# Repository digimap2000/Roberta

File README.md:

# Roberta
Comau NS16 Industrial Robot Conversion

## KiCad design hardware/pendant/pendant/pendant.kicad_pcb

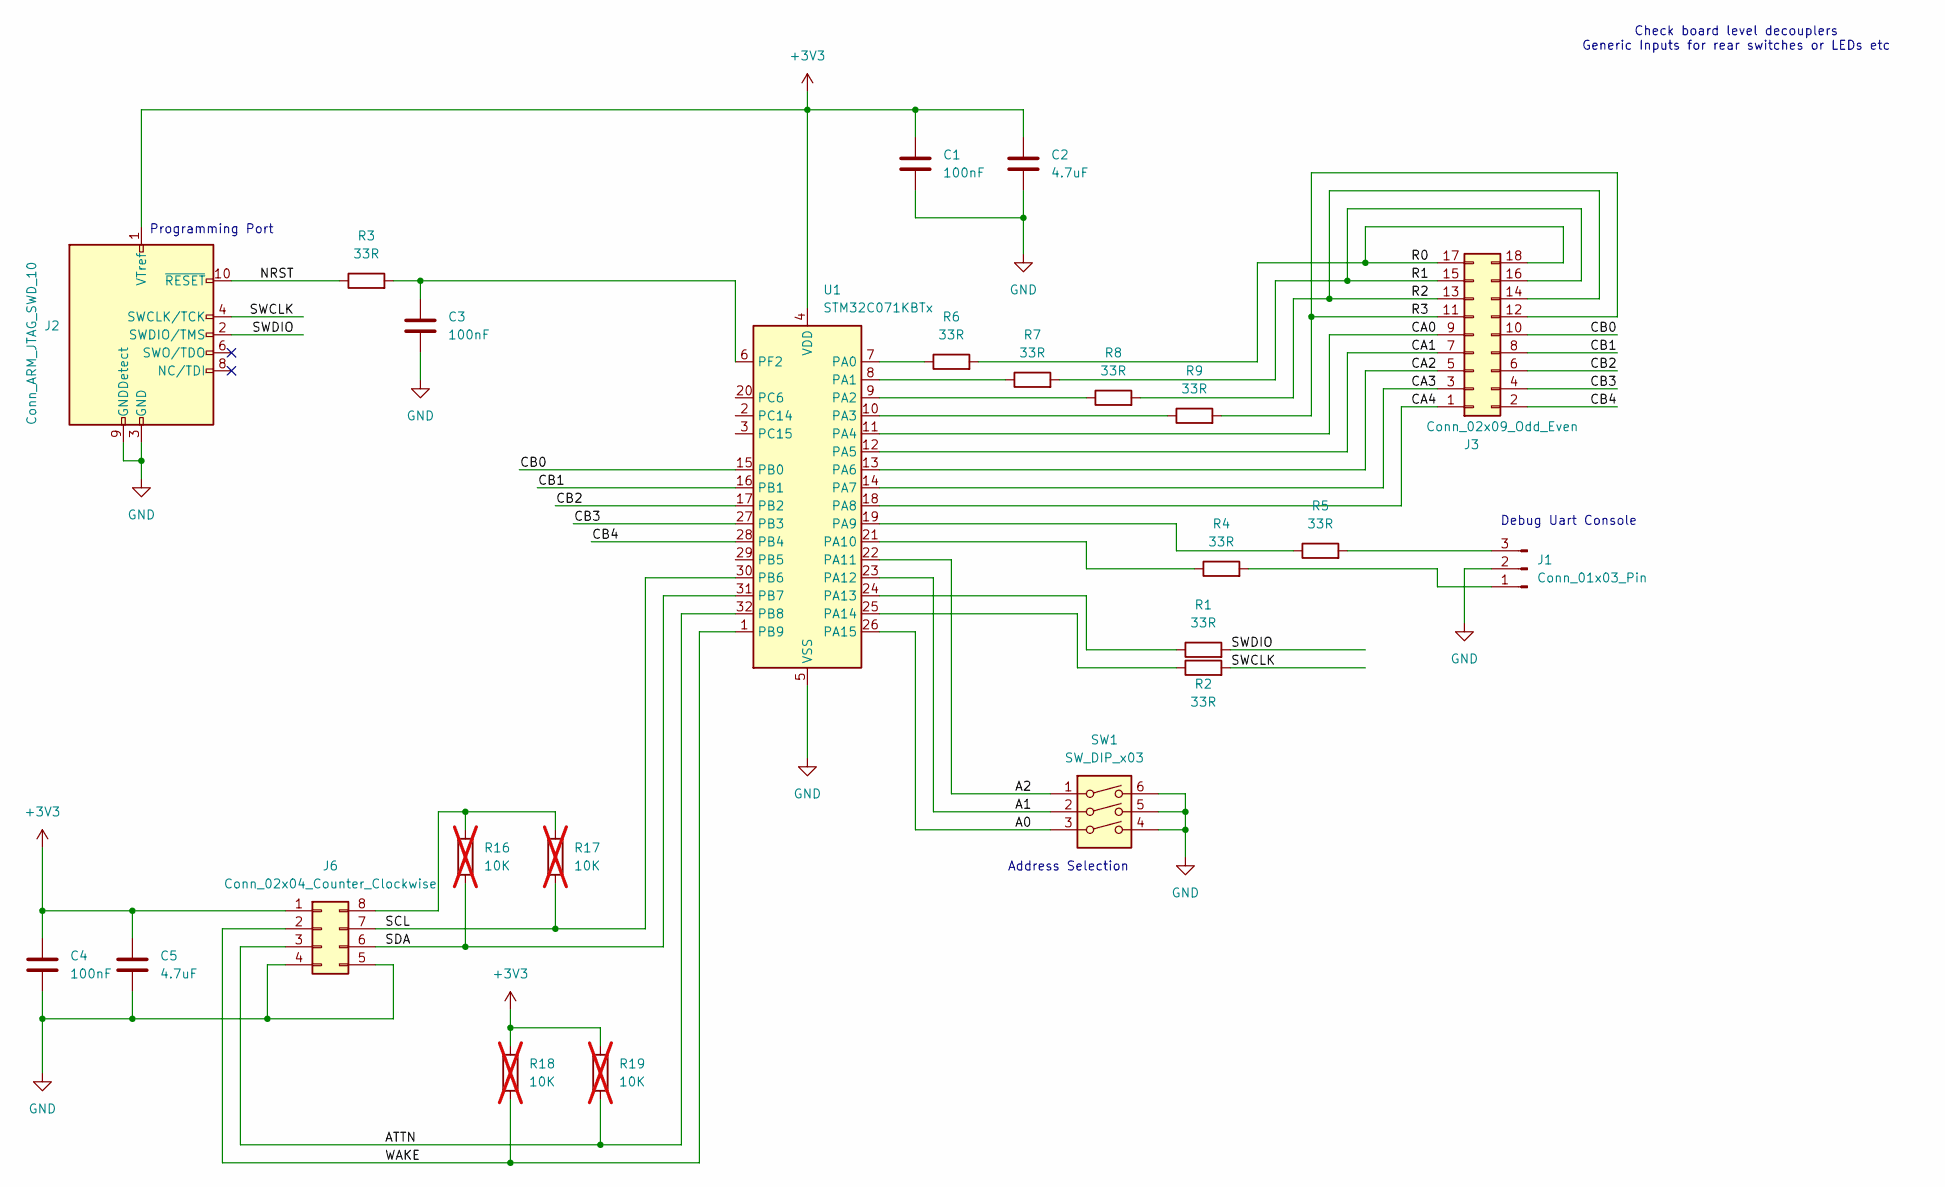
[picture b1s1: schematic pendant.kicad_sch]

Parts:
C1, C3, C4: 100nF; C_0805_2012Metric
C2, C5: 4.7uF; C_0805_2012Metric
J1: Conn_01x03_Pin; PinHeader_1x03_P2.54mm_Vertical
J2: Conn_ARM_JTAG_SWD_10; Tag-Connect_TC2050-IDC-FP_2x05_P1.27mm_Vertical
J3: Conn_02x09_Odd_Even; PinHeader_2x09_P2.54mm_Horizontal
J6: Conn_02x04_Counter_Clockwise; PinHeader_2x04_P2.54mm_Vertical
R1, R2, R3, R4, R5, R6, R7, R8, R9: 33R; R_0805_2012Metric
R16, R17, R18, R19: 10K; R_0805_2012Metric; not fitted
SW1: SW_DIP_x03; DIP-6_W7.62mm
U1: STM32C071KBTx; LQFP-32_7x7mm_P0.8mm

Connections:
+3V3: C1.1, C2.1, C4.1, C5.1, J2.1 (VTref), J6.1, R18.2, R19.2, U1.4 (VDD)
/A0: SW1.3, U1.26 (PA15)
/A1: SW1.2, U1.23 (PA12)
/A2: SW1.1, U1.22 (PA11)
/ATTN: J6.3, R19.1, U1.32 (PB8)
/CA0: J3.9, U1.11 (PA4)
/CA1: J3.7, U1.12 (PA5)
/CA2: J3.5, U1.13 (PA6)
/CA3: J3.3, U1.14 (PA7)
/CA4: J3.1, U1.18 (PA8)
/CB0: J3.10, U1.15 (PB0)
/CB1: J3.8, U1.16 (PB1)
/CB2: J3.6, U1.17 (PB2)
/CB3: J3.4, U1.27 (PB3)
/CB4: J3.2, U1.28 (PB4)
/NRST: J2.10 (~RESET), R3.1
/R0: J3.17, J3.18, R6.2
/R1: J3.15, J3.16, R7.2
/R2: J3.13, J3.14, R8.2
/R3: J3.11, J3.12, R9.2
/SCL: J6.7, R17.1, U1.30 (PB6)
/SDA: J6.6, R16.1, U1.31 (PB7)
/SWCLK: J2.4 (SWCLK/TCK), R2.2
/SWDIO: J2.2 (SWDIO/TMS), R1.2
/WAKE: J6.2, R18.1, U1.1 (PB9)
GND: C1.2, C2.2, C3.2, C4.2, C5.2, J1.2, J2.3 (GND), J2.5 (GND), J2.9 (GNDDetect), J6.4, J6.5, SW1.4, SW1.5, SW1.6, U1.5 (VSS)
unnamed: J1.1, R4.2
unnamed: J1.3, R5.2
unnamed: J6.8, R16.2, R17.2
unnamed: R6.1, U1.7 (PA0)
unnamed: R7.1, U1.8 (PA1)
unnamed: R8.1, U1.9 (PA2)
unnamed: R9.1, U1.10 (PA3)
unnamed: R5.1, U1.19 (PA9)
unnamed: R4.1, U1.21 (PA10)
unnamed: R1.1, U1.24 (PA13)
unnamed: R2.1, U1.25 (PA14)
unnamed: C3.1, R3.2, U1.6 (PF2)

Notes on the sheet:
Debug Uart Console
Check board level decouplers Generic Inputs for rear switches or LEDs etc
Programming Port
Address Selection

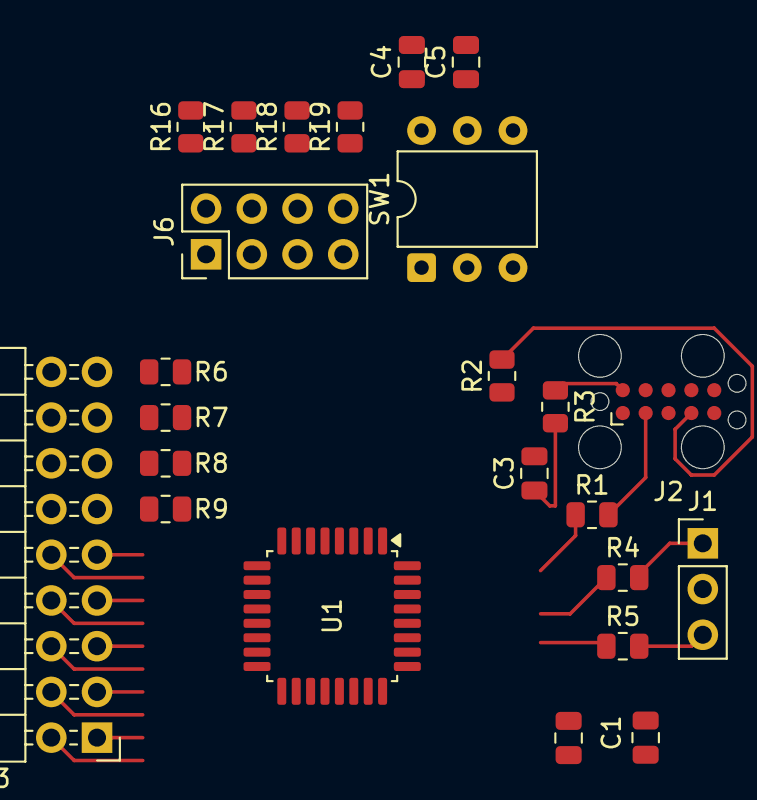
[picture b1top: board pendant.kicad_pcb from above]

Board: 2 copper layers, 24 parts (0 on the bottom side), 38 nets.

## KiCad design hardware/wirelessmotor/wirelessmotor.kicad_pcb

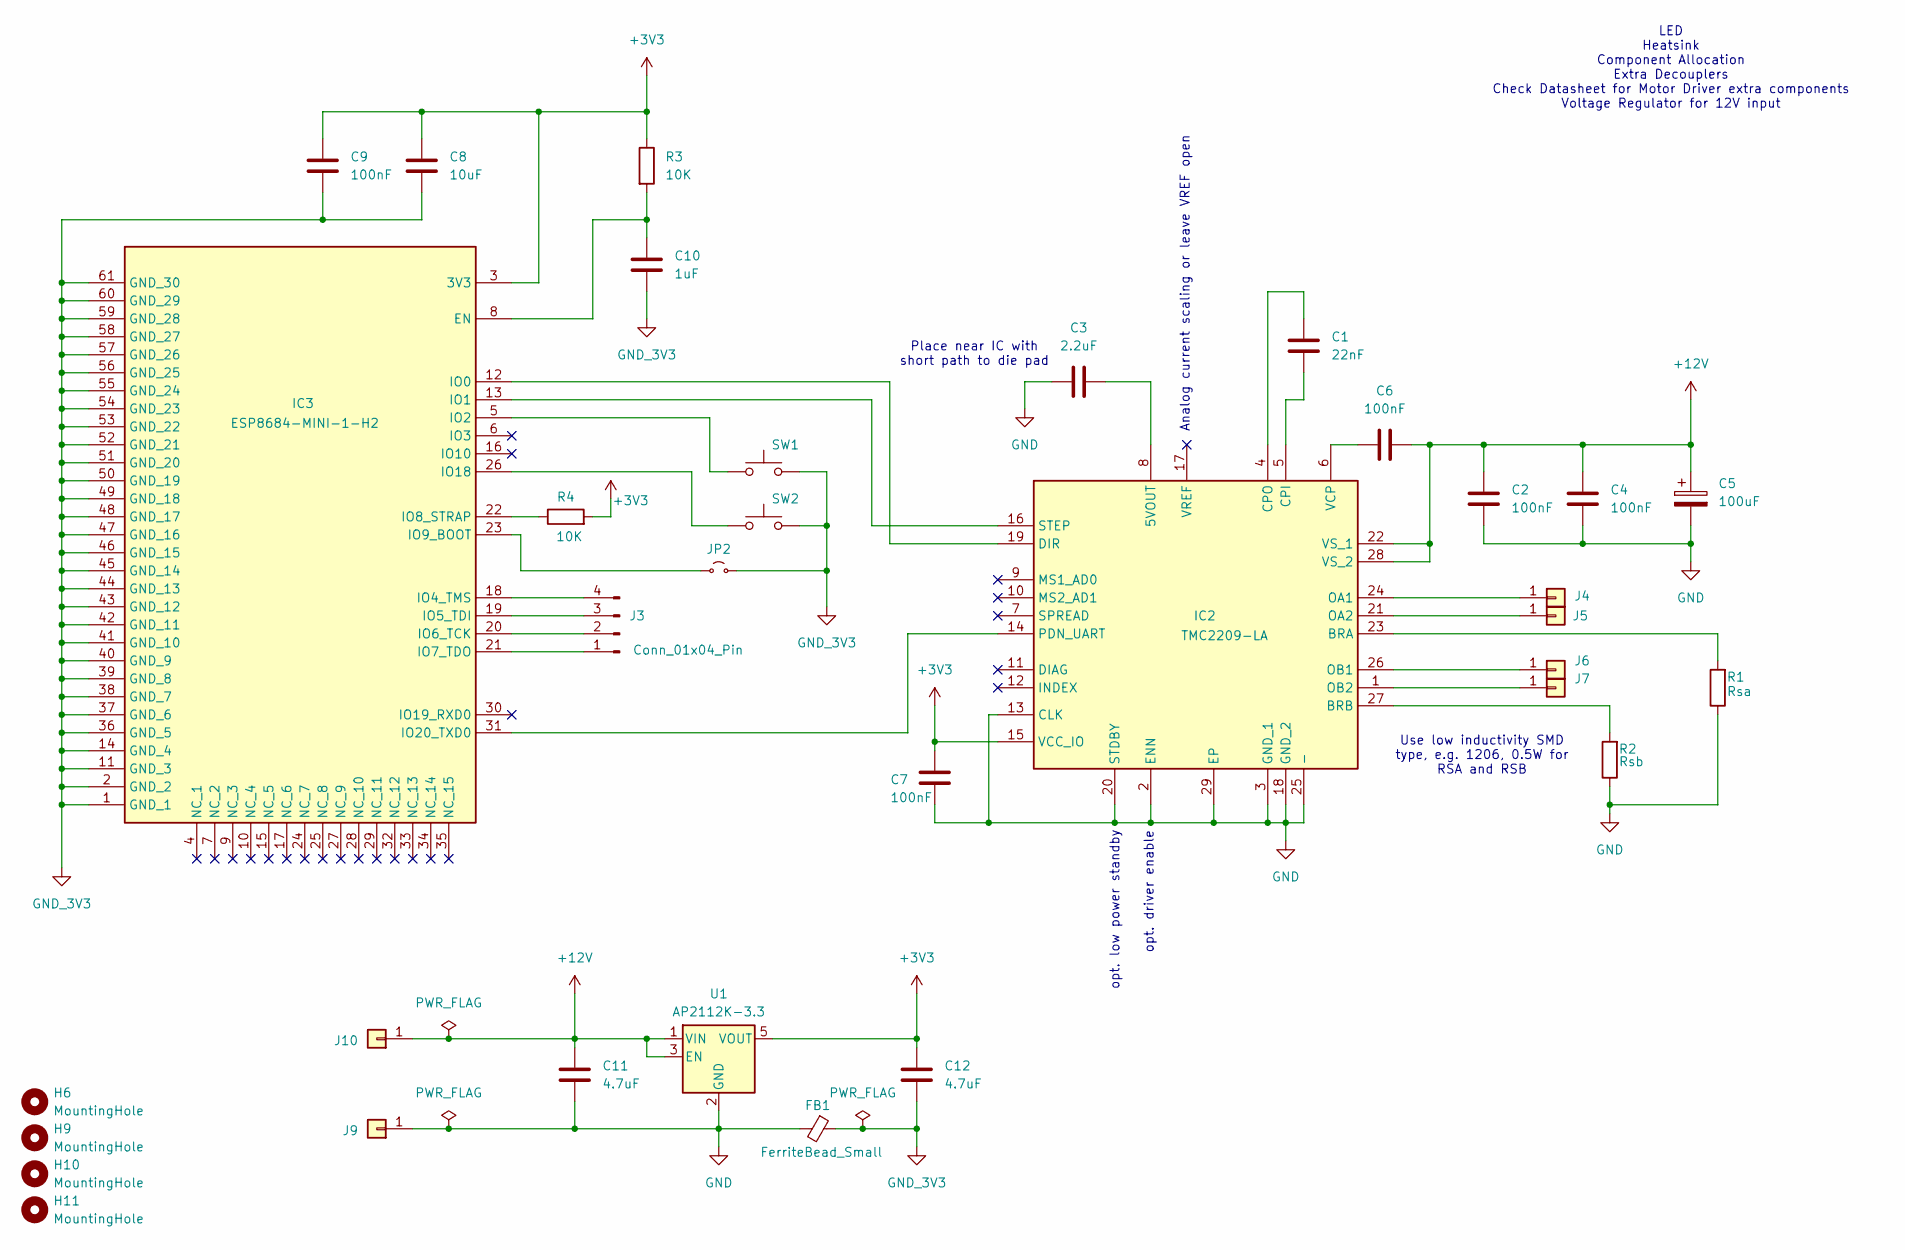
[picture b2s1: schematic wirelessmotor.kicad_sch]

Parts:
C1: 22nF; C_0603_1608Metric
C2, C4, C6, C7, C9: 100nF; C_0603_1608Metric
C3: 2.2uF; C_0603_1608Metric
C5: 100uF; C_0603_1608Metric
C8: 10uF; C_0603_1608Metric
C10: 1uF; C_0603_1608Metric
C11, C12: 4.7uF; C_0603_1608Metric
FB1: FerriteBead_Small; L_Walsin_WLFM201209x
H6, H9, H10, H11: MountingHole; MountingHole_2.2mm_M2_DIN965_Pad
IC2: TMC2209-LA; QFN50P500X500X90-29N; Manufacturer_Part_Number TMC2209-LA; Mouser Part Number 700-TMC2209-LA
IC3: ESP8684-MINI-1-H2; ESP8684MINI1H2; Manufacturer_Part_Number ESP8684-MINI-1-H2; Mouser Part Number 356-ESP8684MINI1H2
J3: Conn_01x04_Pin; PinHeader_1x04_P1.27mm_Vertical
J4: OA1; TestPoint_THTPad_2.5x2.5mm_Drill1.2mm
J5: OA2; TestPoint_THTPad_2.5x2.5mm_Drill1.2mm
J6: 0B1; TestPoint_THTPad_2.5x2.5mm_Drill1.2mm
J7: OB2; TestPoint_THTPad_2.5x2.5mm_Drill1.2mm
J9: 0V; TestPoint_THTPad_2.5x2.5mm_Drill1.2mm
J10: +12V; TestPoint_THTPad_2.5x2.5mm_Drill1.2mm
JP2: Jumper_2_Small_Open; PinHeader_1x02_P1.27mm_Vertical
R1: Rsa; R_0603_1608Metric
R2: Rsb; R_0603_1608Metric
R3, R4: 10K; R_0603_1608Metric
SW1, SW2: SW_Push; PTS636SK43JSMTRLFS
U1: AP2112K-3.3; SOT-23-5

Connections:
+3V3: C7.1, C8.1, C9.1, C12.2, IC2.15 (VCC_IO), IC3.3 (3V3), R3.1, R4.2, U1.5 (VOUT)
+12V: C2.1, C4.1, C5.1, C6.2, C11.2, IC2.22 (VS_1), IC2.28 (VS_2), J10.1, U1.1 (VIN), U1.3 (EN)
GND: C2.2, C3.1, C4.2, C5.2, C7.2, C11.1, FB1.2, IC2.2 (ENN), IC2.3 (GND_1), IC2.13 (CLK), IC2.18 (GND_2), IC2.20 (STDBY), IC2.25 (-), IC2.29 (EP), J9.1, R1.1, R2.1, U1.2 (GND)
GND_3V3: C8.2, C9.2, C10.2, C12.1, FB1.1, IC3.1 (GND_1), IC3.2 (GND_2), IC3.11 (GND_3), IC3.14 (GND_4), IC3.36 (GND_5), IC3.37 (GND_6), IC3.38 (GND_7), IC3.39 (GND_8), IC3.40 (GND_9), IC3.41 (GND_10), IC3.42 (GND_11), IC3.43 (GND_12), IC3.44 (GND_13), IC3.45 (GND_14), IC3.46 (GND_15), IC3.47 (GND_16), IC3.48 (GND_17), IC3.49 (GND_18), IC3.50 (GND_19), IC3.51 (GND_20), IC3.52 (GND_21), IC3.53 (GND_22), IC3.54 (GND_23), IC3.55 (GND_24), IC3.56 (GND_25), IC3.57 (GND_26), IC3.58 (GND_27), IC3.59 (GND_28), IC3.60 (GND_29), IC3.61 (GND_30), JP2.2 (B), SW1.2, SW2.2
unnamed: C3.2, IC2.8 (5VOUT)
unnamed: IC2.23 (BRA), R1.2
unnamed: IC2.27 (BRB), R2.2
unnamed: C1.2, IC2.5 (CPI)
unnamed: C1.1, IC2.4 (CPO)
unnamed: IC2.19 (DIR), IC3.12 (IO0)
unnamed: IC2.24 (OA1), J4.1
unnamed: IC2.21 (OA2), J5.1
unnamed: IC2.26 (OB1), J6.1
unnamed: IC2.1 (OB2), J7.1
unnamed: IC2.14 (PDN_UART), IC3.31 (IO20_TXD0)
unnamed: IC2.16 (STEP), IC3.13 (IO1)
unnamed: C6.1, IC2.6 (VCP)
unnamed: C10.1, IC3.8 (EN), R3.2
unnamed: IC3.5 (IO2), SW1.1
unnamed: IC3.18 (IO4_TMS), J3.4
unnamed: IC3.19 (IO5_TDI), J3.3
unnamed: IC3.20 (IO6_TCK), J3.2
unnamed: IC3.21 (IO7_TDO), J3.1
unnamed: IC3.22 (IO8_STRAP), R4.1
unnamed: IC3.23 (IO9_BOOT), JP2.1 (A)
unnamed: IC3.26 (IO18), SW2.1

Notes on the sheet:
LED Heatsink Component Allocation Extra Decouplers Check Datasheet for Motor Driver extra components Voltage Regulator for 12V input
Use low inductivity SMD type, e.g. 1206, 0.5W for RSA and RSB
opt. low power standby
Place near IC with short path to die pad
Analog current scaling or leave VREF open
opt. driver enable

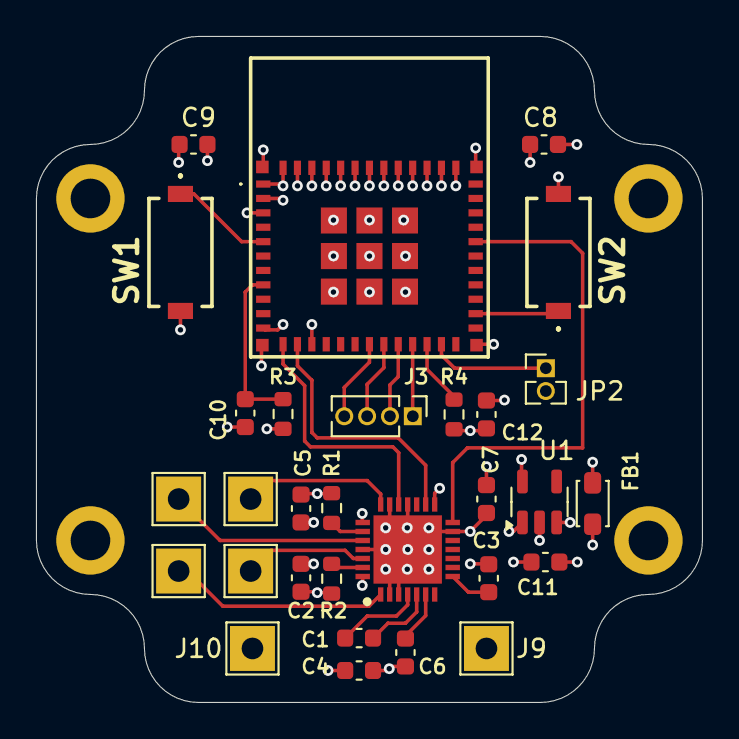
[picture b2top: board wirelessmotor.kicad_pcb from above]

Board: 4 copper layers, 37.0 x 37.0 mm, 34 parts (0 on the bottom side), 26 nets.

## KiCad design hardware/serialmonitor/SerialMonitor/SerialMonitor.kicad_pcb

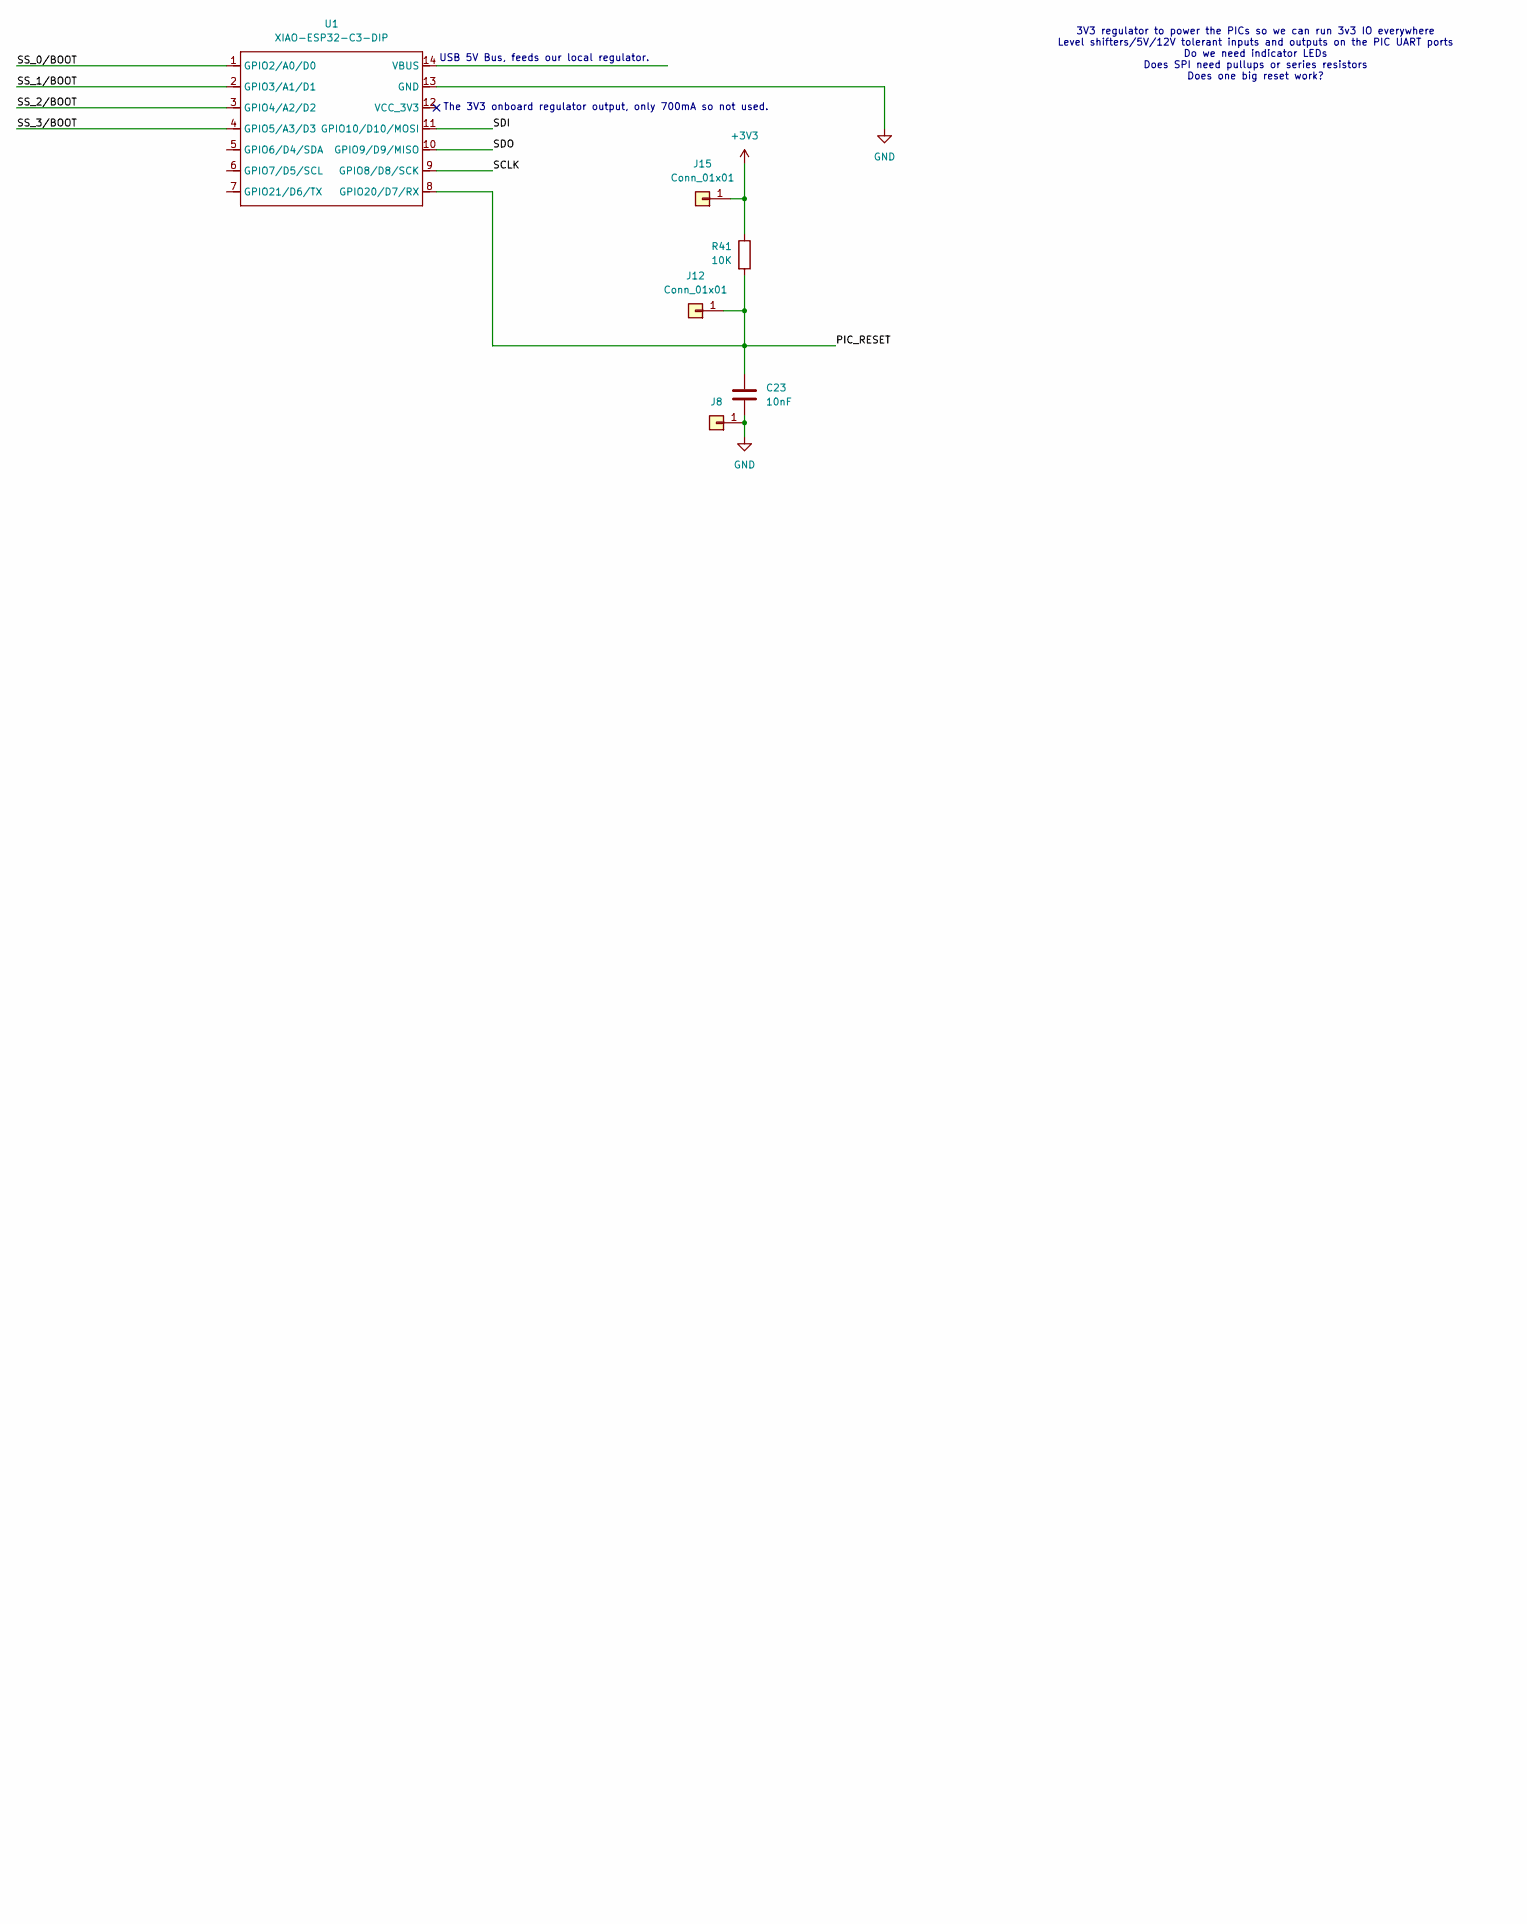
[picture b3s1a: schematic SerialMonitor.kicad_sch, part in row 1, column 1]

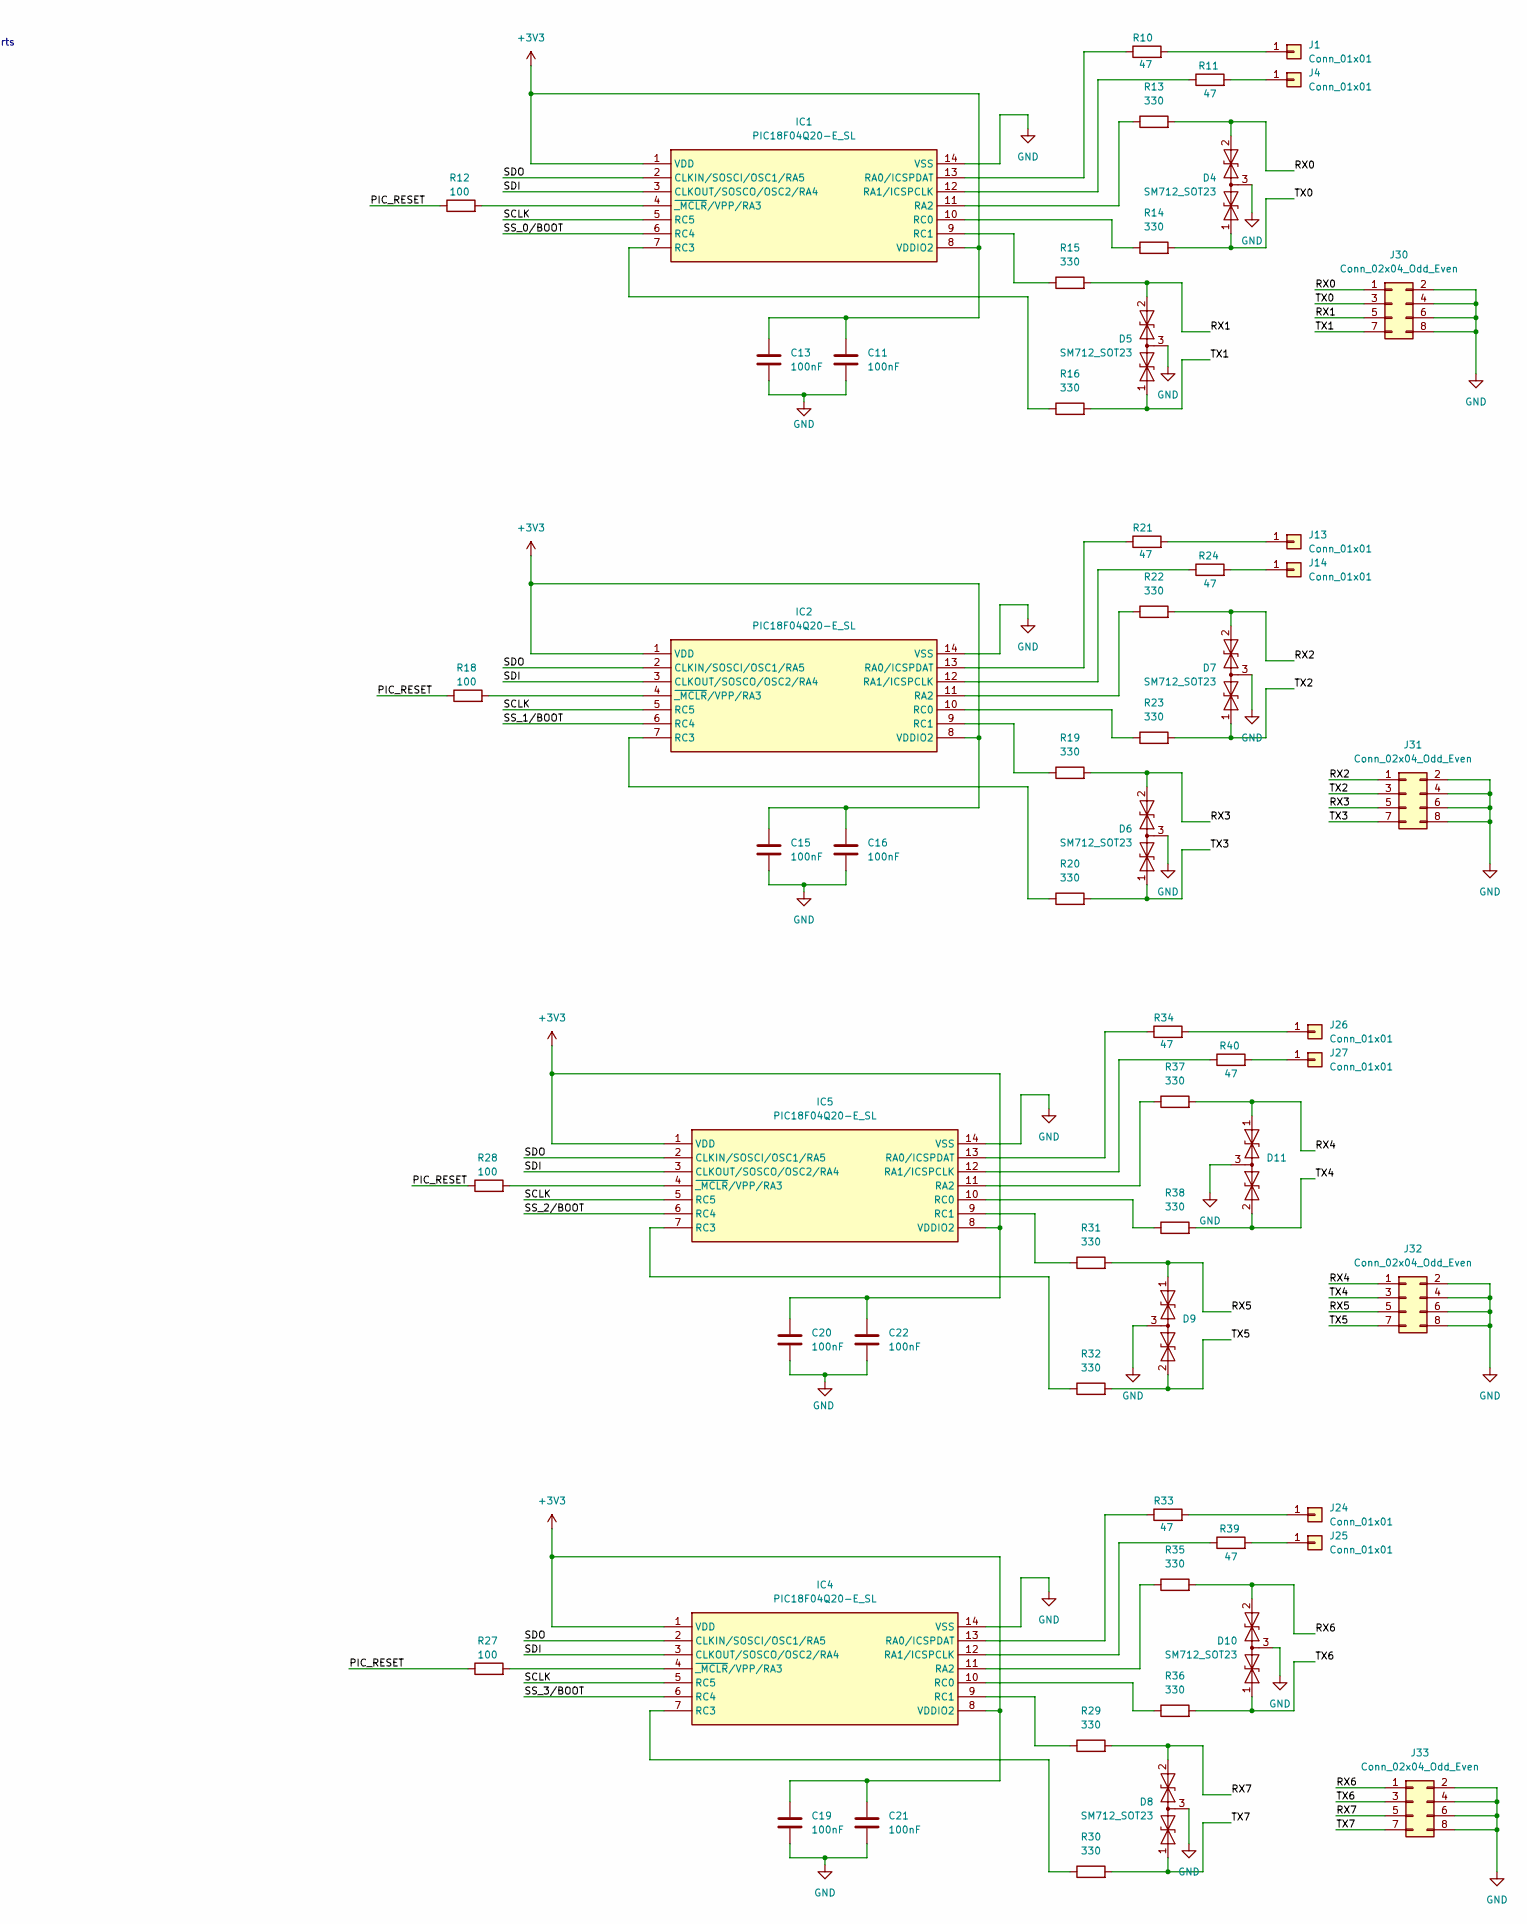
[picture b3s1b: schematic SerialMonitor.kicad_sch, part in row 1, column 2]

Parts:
C11, C13, C15, C16, C19, C20, C21, C22: 100nF; C_0603_1608Metric
C23: 10nF; C_0603_1608Metric
D4, D5, D6, D7, D8, D9, D10, D11: SM712_SOT23; SOT-23; Part SM712-02HTG
IC1, IC2, IC4, IC5: PIC18F04Q20-E_SL; SOIC127P600X175-14N; Manufacturer_Part_Number PIC18F04Q20-E/SL; Mouser Part Number 579-PIC18F04Q20-E/SL
J1, J4, J8, J12, J13, J14, J15, J24, J25, J26, J27: Conn_01x01; TestPoint_Pad_2.0x2.0mm
J30, J31, J32, J33: Conn_02x04_Odd_Even; PinSocket_2x04_P1.27mm_Vertical
R10, R11, R21, R24, R33, R34, R39, R40: 47; R_0603_1608Metric
R12, R18, R27, R28: 100; R_0603_1608Metric
R13, R14, R15, R16, R19, R20, R22, R23, R29, R30, R31, R32, R35, R36, R37, R38: 330; R_0603_1608Metric
R41: 10K; R_0603_1608Metric
U1: XIAO-ESP32-C3-DIP; SeeedStudio_XIAO_ESP32S3

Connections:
+3V3: C11.2, C13.2, C15.2, C16.2, C19.2, C20.2, C21.2, C22.2, IC1.1 (VDD), IC1.8 (VDDIO2), IC2.1 (VDD), IC2.8 (VDDIO2), IC4.1 (VDD), IC4.8 (VDDIO2), IC5.1 (VDD), IC5.8 (VDDIO2), J15.1, R41.1
/PIC_RESET: C23.2, J12.1, R12.1, R18.1, R27.1, R28.1, R41.2, U1.8 (GPIO20/D7/RX)
/RX0: D4.2 (A2), J30.1, R13.2
/RX1: D5.2 (A2), J30.5, R15.2
/RX2: D7.2 (A2), J31.1, R22.2
/RX3: D6.2 (A2), J31.5, R19.2
/RX4: D11.1 (A1), J32.1, R37.2
/RX5: D9.1 (A1), J32.5, R31.2
/RX6: D10.2 (A2), J33.1, R35.2
/RX7: D8.2 (A2), J33.5, R29.2
/SCLK: IC1.5 (RC5), IC2.5 (RC5), IC4.5 (RC5), IC5.5 (RC5), U1.9 (GPIO8/D8/SCK)
/SDI: IC1.3 (CLKOUT/SOSCO/OSC2/RA4), IC2.3 (CLKOUT/SOSCO/OSC2/RA4), IC4.3 (CLKOUT/SOSCO/OSC2/RA4), IC5.3 (CLKOUT/SOSCO/OSC2/RA4), U1.11 (GPIO10/D10/MOSI)
/SDO: IC1.2 (CLKIN/SOSCI/OSC1/RA5), IC2.2 (CLKIN/SOSCI/OSC1/RA5), IC4.2 (CLKIN/SOSCI/OSC1/RA5), IC5.2 (CLKIN/SOSCI/OSC1/RA5), U1.10 (GPIO9/D9/MISO)
/SS_0/BOOT: IC1.6 (RC4), U1.1 (GPIO2/A0/D0)
/SS_1/BOOT: IC2.6 (RC4), U1.2 (GPIO3/A1/D1)
/SS_2/BOOT: IC5.6 (RC4), U1.3 (GPIO4/A2/D2)
/SS_3/BOOT: IC4.6 (RC4), U1.4 (GPIO5/A3/D3)
/TX0: D4.1 (A1), J30.3, R14.2
/TX1: D5.1 (A1), J30.7, R16.2
/TX2: D7.1 (A1), J31.3, R23.2
/TX3: D6.1 (A1), J31.7, R20.2
/TX4: D11.2 (A2), J32.3, R38.2
/TX5: D9.2 (A2), J32.7, R32.2
/TX6: D10.1 (A1), J33.3, R36.2
/TX7: D8.1 (A1), J33.7, R30.2
GND: C11.1, C13.1, C15.1, C16.1, C19.1, C20.1, C21.1, C22.1, C23.1, D4.3 (common), D5.3 (common), D6.3 (common), D7.3 (common), D8.3 (common), D9.3 (common), D10.3 (common), D11.3 (common), IC1.14 (VSS), IC2.14 (VSS), IC4.14 (VSS), IC5.14 (VSS), J8.1, J30.2, J30.4, J30.6, J30.8, J31.2, J31.4, J31.6, J31.8, J32.2, J32.4, J32.6, J32.8, J33.2, J33.4, J33.6, J33.8, U1.13 (GND)
unnamed: IC1.13 (RA0/ICSPDAT), R10.1
unnamed: IC1.12 (RA1/ICSPCLK), R11.1
unnamed: IC1.11 (RA2), R13.1
unnamed: IC1.10 (RC0), R14.1
unnamed: IC1.9 (RC1), R15.1
unnamed: IC1.7 (RC3), R16.1
unnamed: IC1.4 (~_MCLR/VPP/RA3), R12.2
unnamed: IC2.13 (RA0/ICSPDAT), R21.1
unnamed: IC2.12 (RA1/ICSPCLK), R24.1
unnamed: IC2.11 (RA2), R22.1
unnamed: IC2.10 (RC0), R23.1
unnamed: IC2.9 (RC1), R19.1
unnamed: IC2.7 (RC3), R20.1
unnamed: IC2.4 (~_MCLR/VPP/RA3), R18.2
unnamed: IC4.13 (RA0/ICSPDAT), R33.1
unnamed: IC4.12 (RA1/ICSPCLK), R39.1
unnamed: IC4.11 (RA2), R35.1
unnamed: IC4.10 (RC0), R36.1
unnamed: IC4.9 (RC1), R29.1
unnamed: IC4.7 (RC3), R30.1
unnamed: IC4.4 (~_MCLR/VPP/RA3), R27.2
unnamed: IC5.13 (RA0/ICSPDAT), R34.1
unnamed: IC5.12 (RA1/ICSPCLK), R40.1
unnamed: IC5.11 (RA2), R37.1
unnamed: IC5.10 (RC0), R38.1
unnamed: IC5.9 (RC1), R31.1
unnamed: IC5.7 (RC3), R32.1
unnamed: IC5.4 (~_MCLR/VPP/RA3), R28.2
unnamed: J1.1, R10.2
unnamed: J4.1, R11.2
unnamed: J13.1, R21.2
unnamed: J14.1, R24.2
unnamed: J24.1, R33.2
unnamed: J25.1, R39.2
unnamed: J26.1, R34.2
unnamed: J27.1, R40.2

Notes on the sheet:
USB 5V Bus, feeds our local regulator.
3V3 regulator to power the PICs so we can run 3v3 IO everywhere Level shifters/5V/12V tolerant inputs and outputs on the PIC UART ports Do we need indicator LEDs Does SPI need pullups or series resistors Does one big reset work?
The 3V3 onboard regulator output, only 700mA so not used.

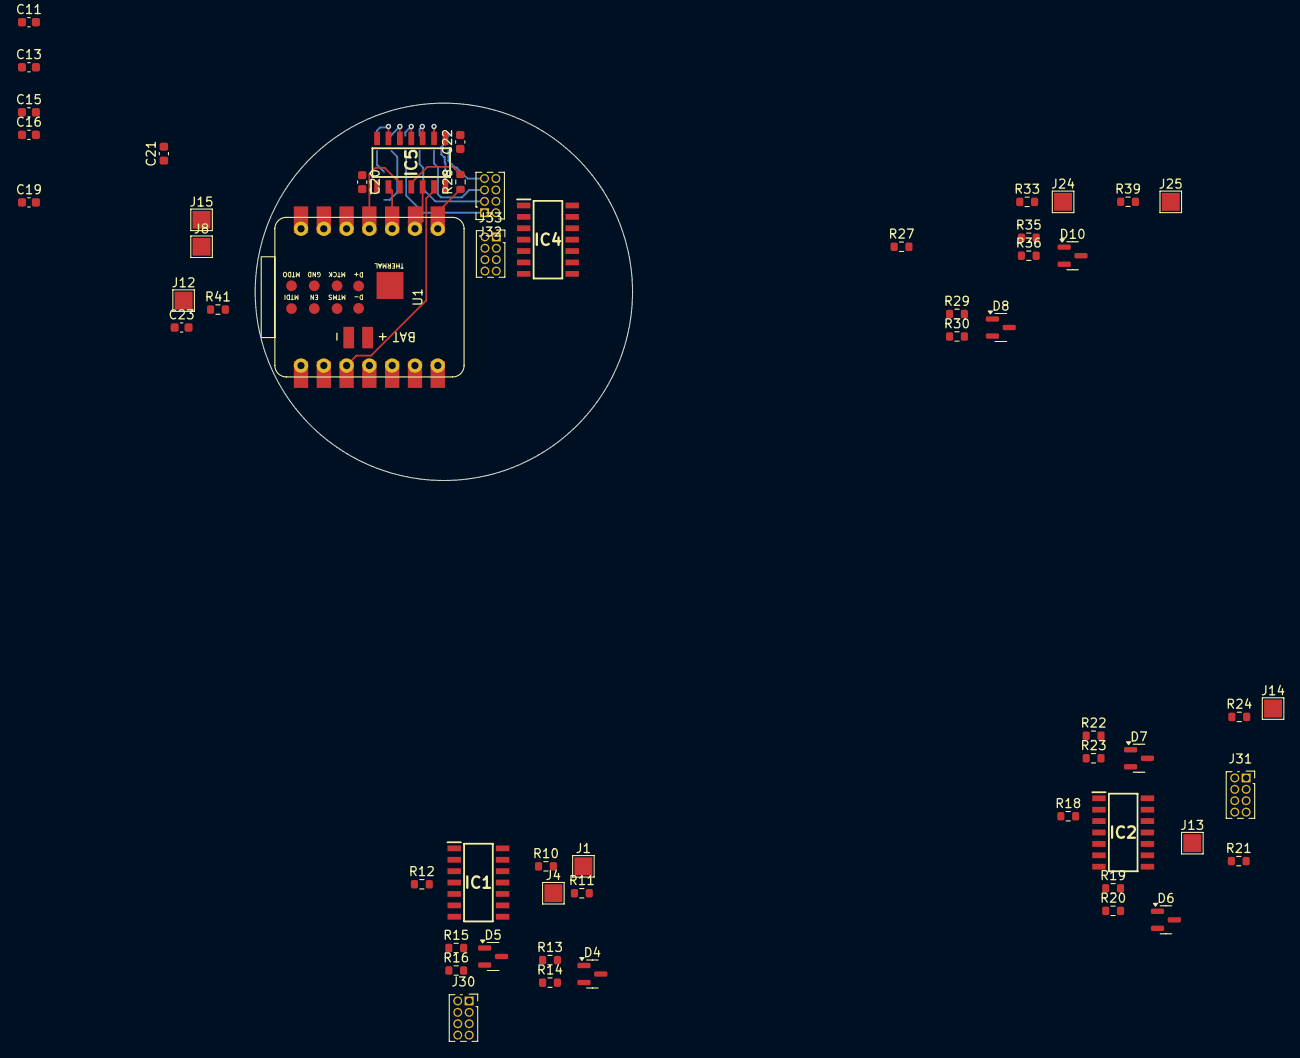
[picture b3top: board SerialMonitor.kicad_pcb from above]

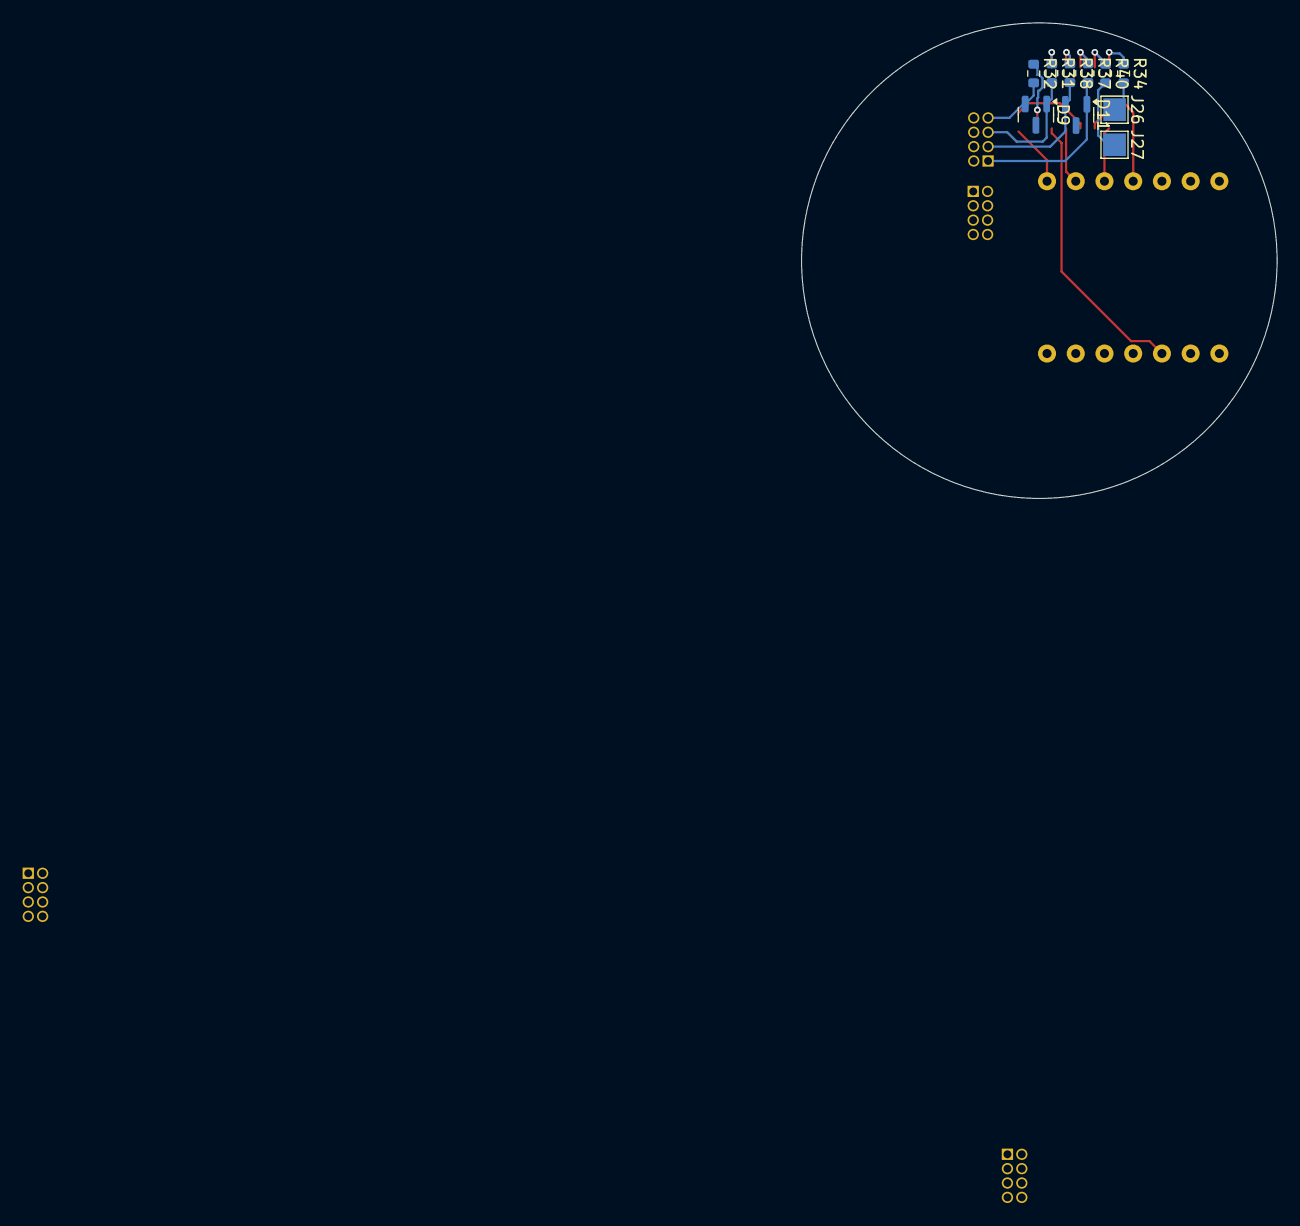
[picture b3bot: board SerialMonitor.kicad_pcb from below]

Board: 2 copper layers, 42.0 x 42.0 mm, 66 parts (10 on the bottom side), 62 nets.
